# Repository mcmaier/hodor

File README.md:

# HODOR
**H**ighly flexible, **O**pen-source **D**oor **O**peration **R**egulator — HODOR holds your door!

## Overview

HODOR is a universal controller for sliding door and roller shutter motor systems. It drives brushed DC motors (12–24 V) using an ESP32-S3 as the main controller with an H-bridge motor driver. Built-in Wi-Fi makes smart home integration straightforward.

## Repository Structure

This is the main repository containing project-level documentation and release bundles. Hardware and software development happen in dedicated sub-repositories, included here as Git submodules:

| Repository | Description |
|---|---|
| [hodor-hardware](https://github.com/mcmaier/hodor-hardware) | KiCad 9 schematic & PCB design |
| [hodor-software](https://github.com/mcmaier/hodor-software) | ESP-IDF firmware (C, ESP32-S3) |

### Directory Layout

```
hodor/
├── documentation/       Project-level documentation (block diagrams, specs)
├── releases/            Matched HW/SW release bundles
│   └── v0.1.0/          Example: Gerbers + firmware binary for a release
├── hodor-hardware/      Git submodule → mcmaier/hodor-hardware
├── hodor-software/      Git submodule → mcmaier/hodor-software
└── README.md
```

## Getting Started

Clone with submodules:

```bash
git clone --recurse-submodules https://github.com/mcmaier/hodor.git
```

Or, if already cloned:

```bash
git submodule update --init --recursive
```

## Releases

The `releases/` directory contains matched hardware and software versions that are tested together. Each release folder includes the relevant Gerber files, BOM, and firmware binary.

## License

This project is licensed under the MIT License — see the [LICENSE](LICENSE) file for details.

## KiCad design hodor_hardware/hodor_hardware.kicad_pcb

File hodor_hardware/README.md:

# _HODOR - Highly-flexible Open-Source Door Operation Regulator_

Description will be added soon.

## Folder contents

The project **Hodor Hardware** contains hardware design files for the PCBs, which where created in KiCAD 9.0.

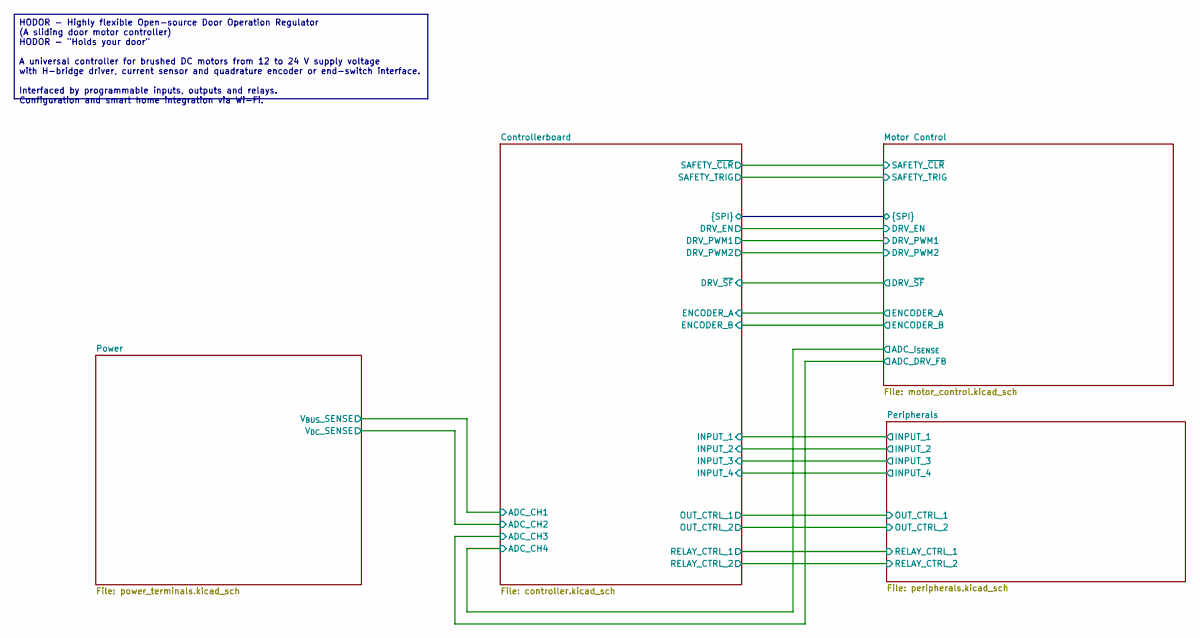
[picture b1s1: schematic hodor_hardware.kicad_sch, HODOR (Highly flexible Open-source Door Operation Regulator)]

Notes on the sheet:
HODOR - Highly flexible Open-source Door Operation Regulator (A sliding door motor controller) HODOR - "Holds your door" A universal controller for brushed DC motors from 12 to 24 V supply voltage with H-bridge driver, current sensor and quadrature encoder or end-switch interface. Interfaced by pro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

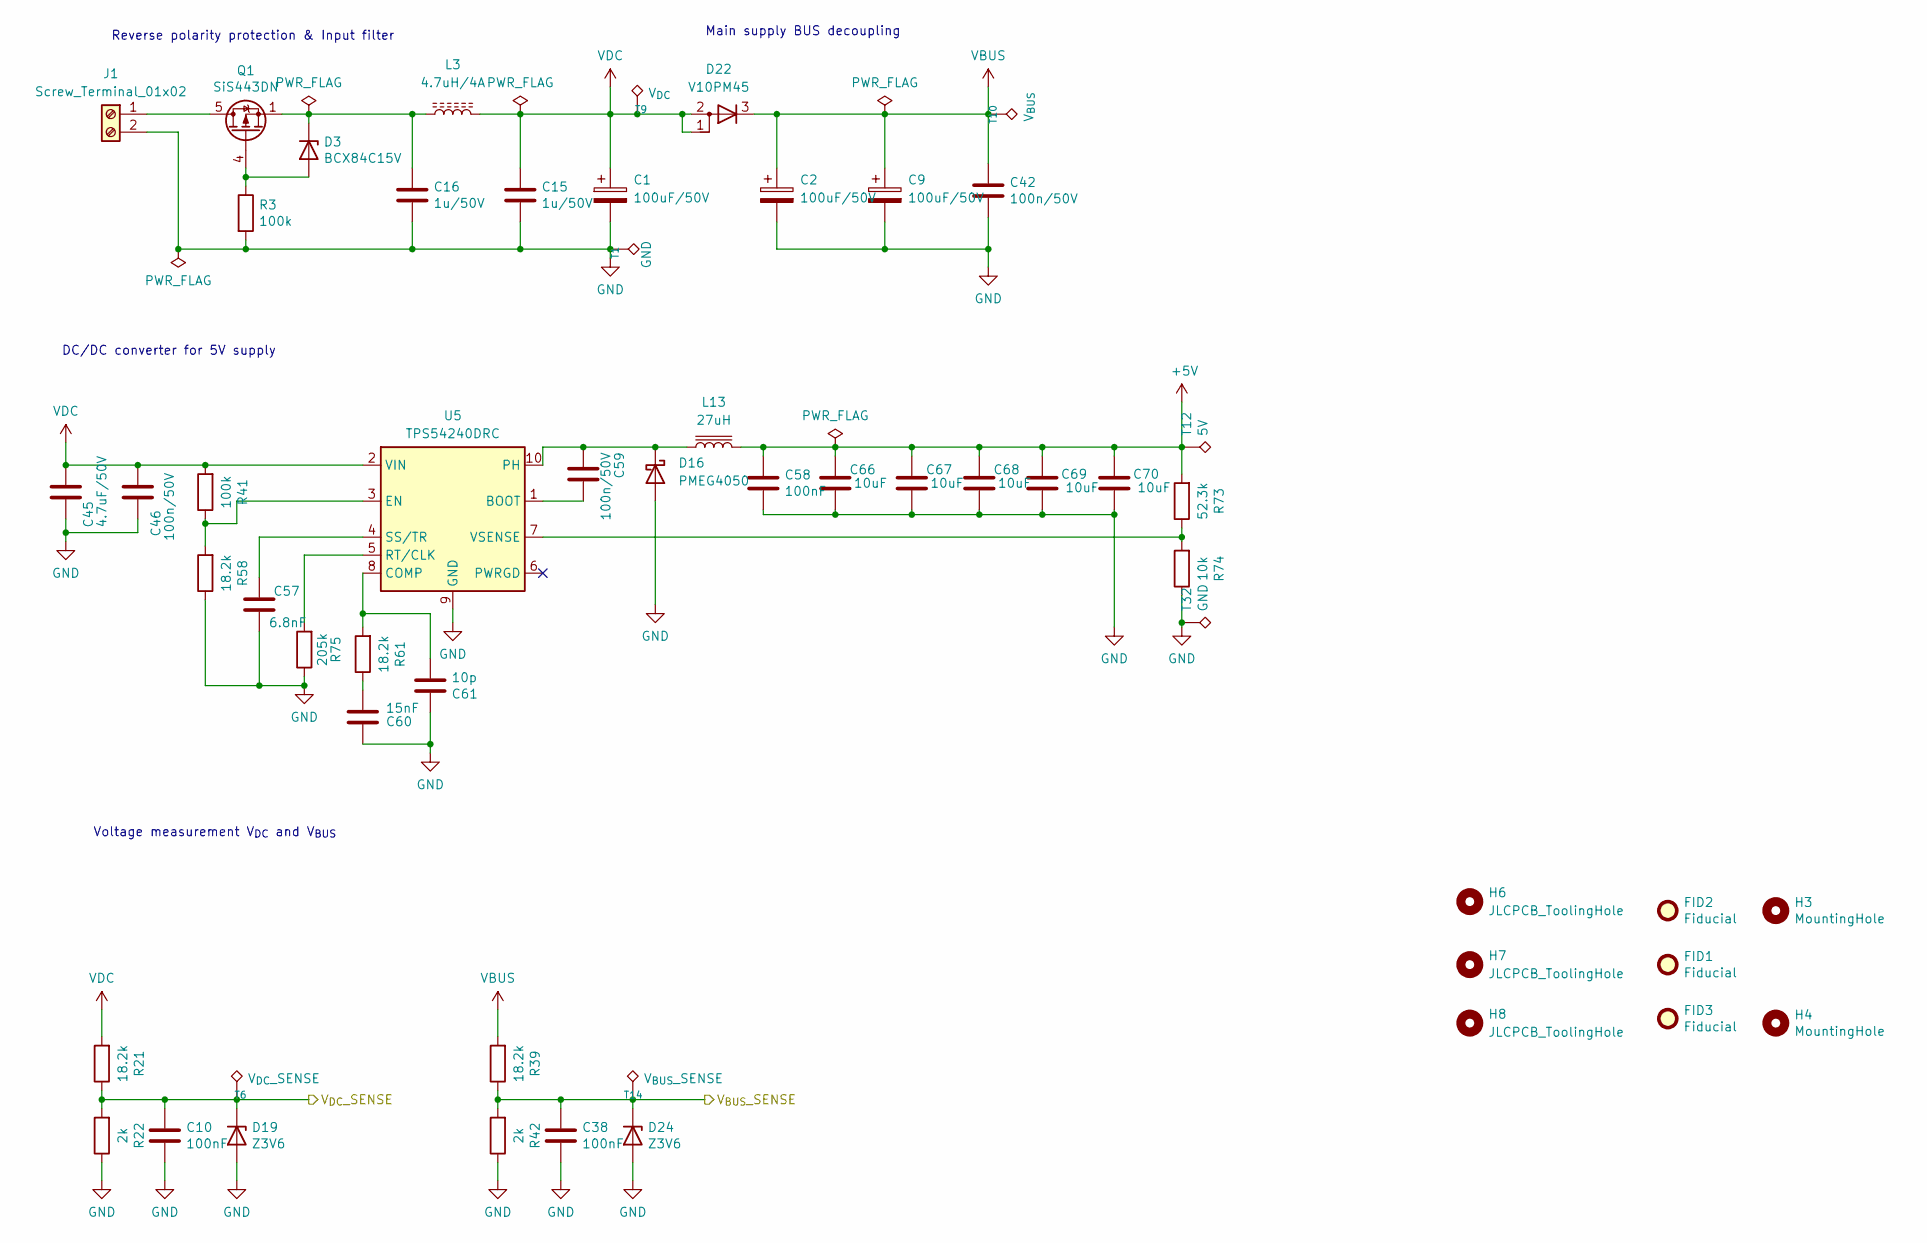
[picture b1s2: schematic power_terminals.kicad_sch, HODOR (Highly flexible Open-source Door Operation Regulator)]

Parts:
C1, C2, C9: 100uF/50V; C_Elec_8x10.2
C10, C38, C58: 100nF; C_0402_1005Metric
C15, C16: 1u/50V; C_0805_2012Metric
C42, C46, C59: 100n/50V; C_0603_1608Metric
C45: 4.7uF/50V; C_1206_3216Metric
C57: 6.8nF; C_0402_1005Metric
C60: 15nF; C_0402_1005Metric
C61: 10p; C_0402_1005Metric
C66, C67, C68, C69, C70: 10uF; C_0805_2012Metric
D3: BCX84C15V; D_SOD-523
D16: PMEG4050; D_SMB
D19, D24: Z3V6; D_SOD-523
D22: V10PM45; TO-277A
FID1, FID2, FID3: Fiducial; Fiducial_1mm_Mask2mm
H3, H4: MountingHole; MountingHole_3.2mm_M3
H6, H7, H8: JLCPCB_ToolingHole
J1: Screw_Terminal_01x02; TerminalBlock_Phoenix_MKDS-1,5-2_1x02_P5.00mm_Horizontal
L3: 4.7uH/4A; L_Wuerth_MAPI-4020
L13: 27uH; L_Wuerth_WE-PD-Typ-7345
Q1: SiS443DN; Vishay_PowerPAK_1212-8_Single
R3, R41: 100k; R_0402_1005Metric
R21, R39, R58, R61: 18.2k; R_0402_1005Metric
R22, R42: 2k; R_0402_1005Metric
R73: 52.3k; R_0402_1005Metric
R74: 10k; R_0402_1005Metric
R75: 205k; R_0402_1005Metric
T1, T32: GND; TestPoint_Pad_1.0x1.0mm
T6: V_{DC}_SENSE; TestPoint_Pad_D1.0mm
T9: V_{DC}; TestPoint_Pad_D1.0mm
T10: V_{BUS}; TestPoint_Pad_D1.0mm
T12: 5V; TestPoint_Pad_D1.0mm
T14: V_{BUS}_SENSE; TestPoint_Pad_D1.0mm
U5: TPS54240DRC; Texas_DRC0010J_ThermalVias

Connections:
+5V: C58.1, C66.1, C67.1, C68.1, C69.1, C70.1, L13.2, R73.2, T12.1; also elsewhere on the board
/Controllerboard/ADC_CH1: C38.1, D24.1 (K), R39.1, R42.2, T14.1; also elsewhere on the board
/Controllerboard/ADC_CH2: C10.1, D19.1 (K), R21.1, R22.2, T6.1; also elsewhere on the board
GND: C1.2, C2.2, C9.2, C10.2, C15.2, C16.2, C38.2, C42.2, C45.2, C46.2, C57.2, C58.2, C60.1, C61.1, C66.2, C67.2, C68.2, C69.2, C70.2, D16.2 (A), D19.2 (A), D24.2 (A), J1.2, R3.2, R22.1, R42.1, R58.1, R74.1, R75.1, T1.1, T32.1, U5.9 (GND), U5.11 (GND); also elsewhere on the board
unnamed: C60.2, R61.1
unnamed: D3.2 (A), Q1.4 (G), R3.1
unnamed: C16.1, D3.1 (K), L3.1, Q1.1 (S), Q1.2 (S), Q1.3 (S)
unnamed: C59.2, D16.1 (K), L13.1, U5.10 (PH)
unnamed: J1.1, Q1.5 (D)
unnamed: C59.1, U5.1 (BOOT)
unnamed: C61.2, R61.2, U5.8 (COMP)
unnamed: R41.1, R58.2, U5.3 (EN)
unnamed: R75.2, U5.5 (RT/CLK)
unnamed: C57.1, U5.4 (SS/TR)
unnamed: R73.1, R74.2, U5.7 (VSENSE)
VBUS: C2.1, C9.1, C42.1, D22.3 (K), R39.2, T10.1; also elsewhere on the board
VDC: C1.1, C15.1, C45.1, C46.1, D22.1 (A), D22.2 (A), L3.2, R21.2, R41.2, T9.1, U5.2 (VIN); also elsewhere on the board

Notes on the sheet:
DC/DC converter for 5V supply
Voltage measurement V_{DC} and V_{BUS}
Reverse polarity protection & Input filter
Main supply BUS decoupling

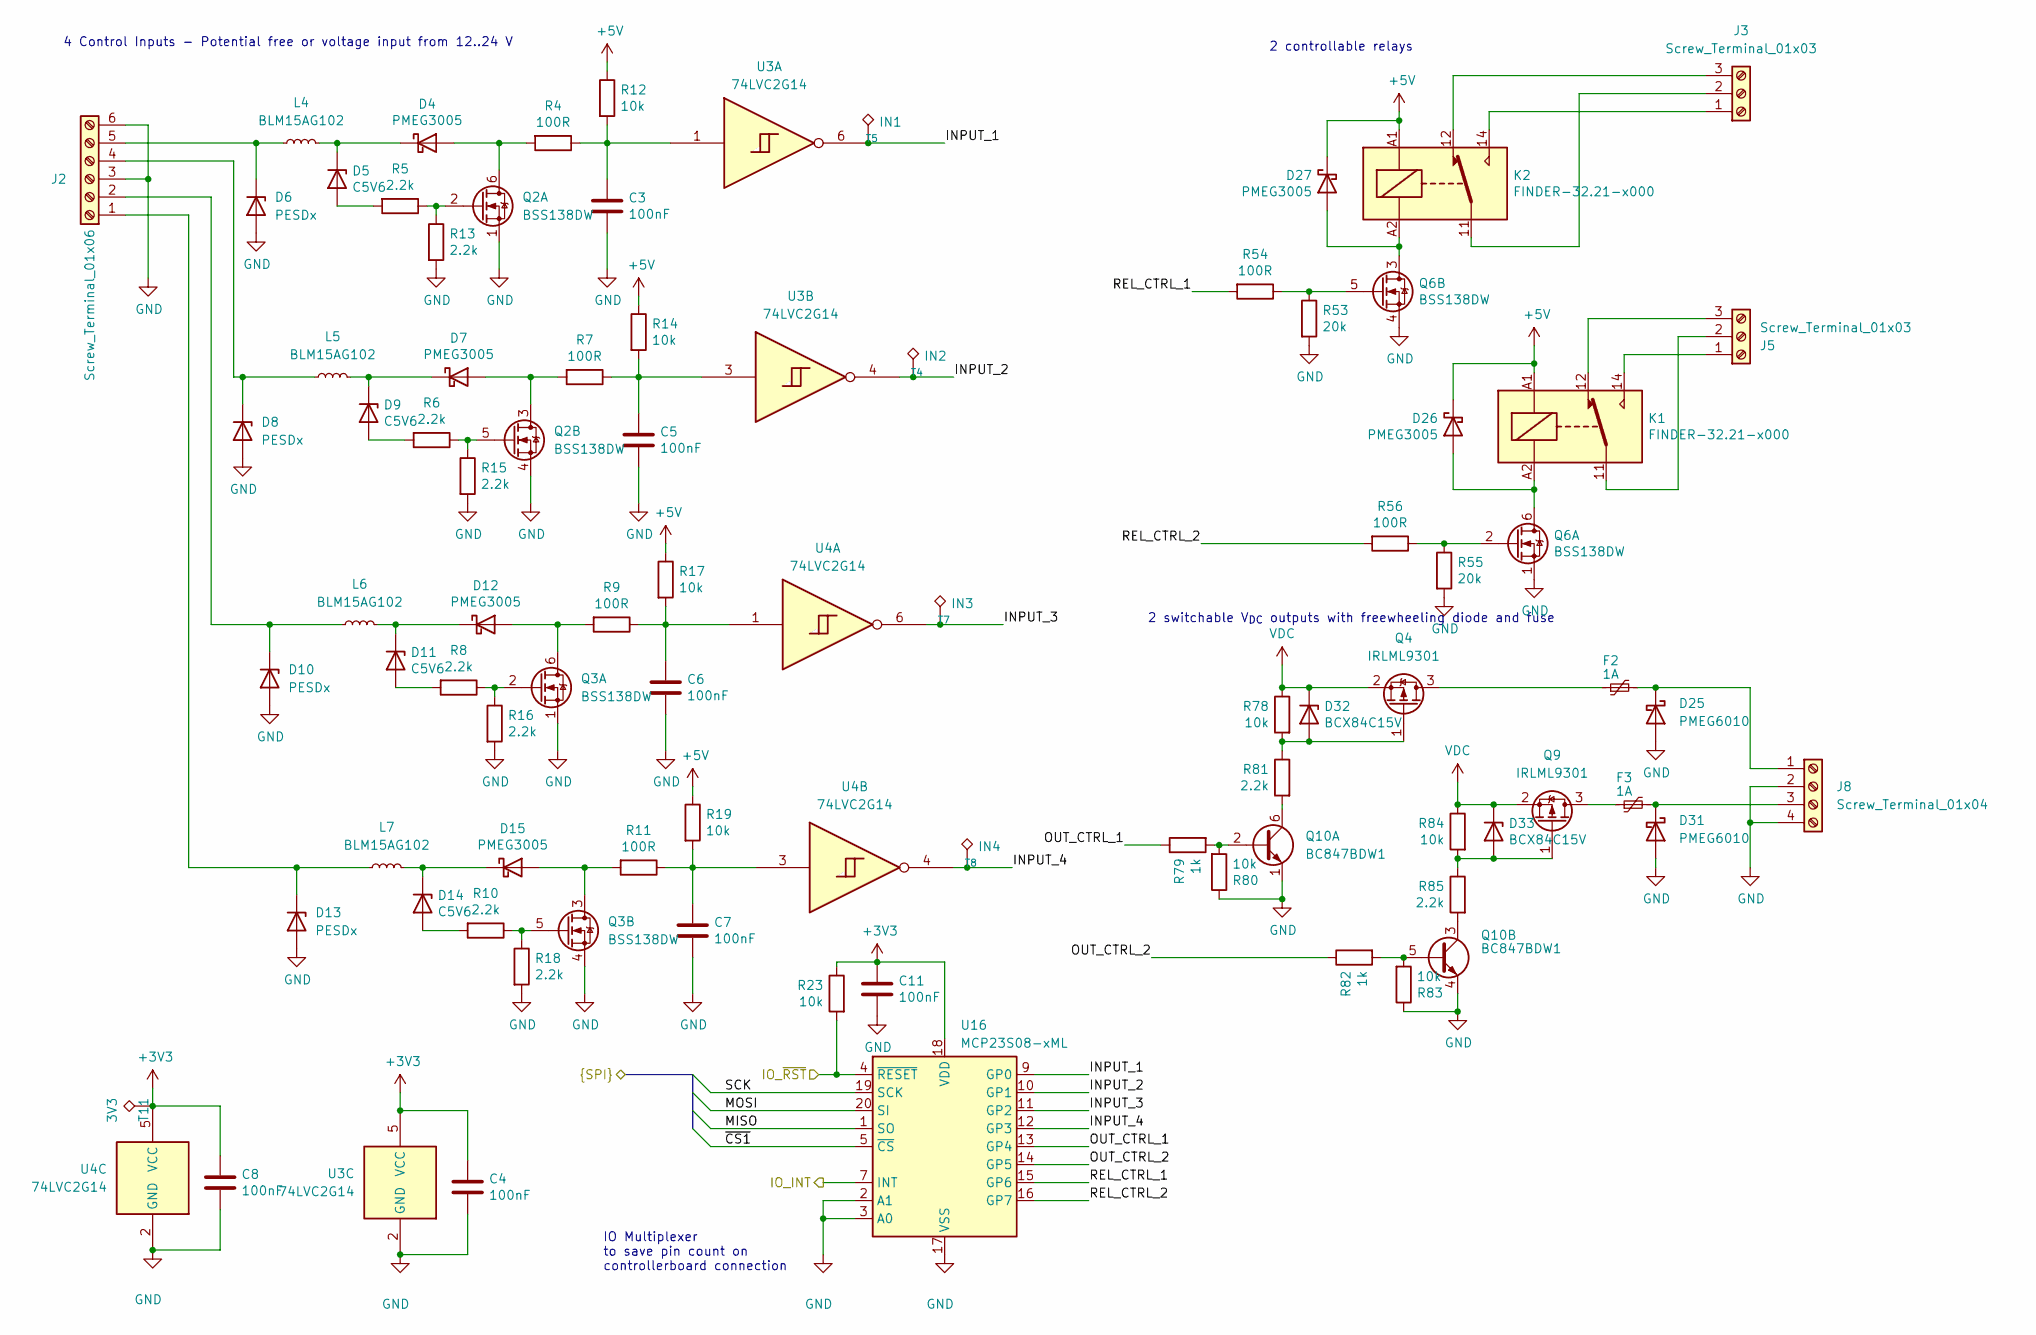
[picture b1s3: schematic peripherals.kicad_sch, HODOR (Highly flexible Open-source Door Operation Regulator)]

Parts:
C3, C4, C5, C6, C7, C8, C11: 100nF; C_0402_1005Metric
D4, D7, D12, D15, D26, D27: PMEG3005; D_SOD-523
D5, D9, D11, D14: C5V6; D_SOD-523
D6, D8, D10, D13: PESDx; Nexperia_DSN1608-2_1.6x0.8mm
D25, D31: PMEG6010; D_SOD-123F
D32, D33: BCX84C15V; D_SOD-523
F2, F3: 1A; Fuse_1210_3225Metric
J2: Screw_Terminal_01x06; TerminalBlock_Phoenix_MKDS-1,5-6_1x06_P5.00mm_Horizontal
J3, J5: Screw_Terminal_01x03; TerminalBlock_Phoenix_MKDS-1,5-3_1x03_P5.00mm_Horizontal
J8: Screw_Terminal_01x04; TerminalBlock_Phoenix_MKDS-1,5-4_1x04_P5.00mm_Horizontal
K1, K2: FINDER-32.21-x000; Relay_SPDT_Finder_32.21-x000
L4, L5, L6, L7: BLM15AG102; L_0402_1005Metric
Q2, Q3, Q6: BSS138DW; SOT-363_SC-70-6
Q4, Q9: IRLML9301; SOT-23
Q10: BC847BDW1; SOT-363_SC-70-6
R4, R7, R9, R11, R54, R56: 100R; R_0402_1005Metric
R5, R6, R8, R10, R13, R15, R16, R18, R81, R85: 2.2k; R_0402_1005Metric
R12, R14, R17, R19, R23, R78, R80, R83, R84: 10k; R_0402_1005Metric
R53, R55: 20k; R_0402_1005Metric
R79, R82: 1k; R_0402_1005Metric
T4: IN2; TestPoint_Pad_D1.0mm
T5: IN1; TestPoint_Pad_D1.0mm
T7: IN3; TestPoint_Pad_D1.0mm
T8: IN4; TestPoint_Pad_D1.0mm
T11: 3V3; TestPoint_Pad_D1.0mm
U3, U4: 74LVC2G14; SOT-23-6
U16: MCP23S08-xML; QFN-20-1EP_4x4mm_P0.5mm_EP2.7x2.7mm

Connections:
+3V3: C4.1, C8.1, C11.1, R23.1, T11.1, U3.5 (VCC), U4.5 (VCC), U16.18 (VDD); also elsewhere on the board
+5V: D26.1 (K), D27.1 (K), K1.A1, K2.A1, R12.1, R14.1, R17.1, R19.1; also elsewhere on the board
/Controllerboard/IO_INT: U16.7 (INT); also elsewhere on the board
/Controllerboard/IO_~RST: R23.2, U16.4 (~RESET); also elsewhere on the board
/Controllerboard/MISO: U16.1 (SO); also elsewhere on the board
/Controllerboard/MOSI: U16.20 (SI); also elsewhere on the board
/Controllerboard/SCK: U16.19 (SCK); also elsewhere on the board
/Controllerboard/~CS1: U16.5 (~CS); also elsewhere on the board
/Peripherals/INPUT_1: T5.1, U3.6, U16.9 (GP0)
/Peripherals/INPUT_2: T4.1, U3.4, U16.10 (GP1)
/Peripherals/INPUT_3: T7.1, U4.6, U16.11 (GP2)
/Peripherals/INPUT_4: T8.1, U4.4, U16.12 (GP3)
/Peripherals/OUT_CTRL_1: R79.1, U16.13 (GP4)
/Peripherals/OUT_CTRL_2: R82.1, U16.14 (GP5)
/Peripherals/REL_CTRL_1: R54.2, U16.15 (GP6)
/Peripherals/REL_CTRL_2: R56.2, U16.16 (GP7)
GND: C3.2, C4.2, C5.2, C6.2, C7.2, C8.2, C11.2, D6.2 (A), D8.2 (A), D10.2 (A), D13.2 (A), D25.2 (A), D31.2 (A), J2.3, J2.6, J8.2, J8.4, Q2.1 (S), Q2.4 (S), Q3.1 (S), Q3.4 (S), Q6.1 (S), Q6.4 (S), Q10.1 (E1), Q10.4 (E2), R13.2, R15.2, R16.2, R18.2, R53.2, R55.2, R80.1, R83.1, U3.2 (GND), U4.2 (GND), U16.2 (A1), U16.3 (A0), U16.17 (VSS); also elsewhere on the board
unnamed: C3.1, R4.1, R12.2, U3.1
unnamed: C5.1, R7.1, R14.2, U3.3
unnamed: C6.1, R9.1, R17.2, U4.1
unnamed: C7.1, R11.1, R19.2, U4.3
unnamed: D4.2 (A), Q2.6 (D), R4.2
unnamed: D4.1 (K), D5.1 (K), L4.2
unnamed: D5.2 (A), R5.2
unnamed: D6.1 (K), J2.5, L4.1
unnamed: D7.2 (A), Q2.3 (D), R7.2
unnamed: D7.1 (K), D9.1 (K), L5.2
unnamed: D8.1 (K), J2.4, L5.1
unnamed: D9.2 (A), R6.2
unnamed: D10.1 (K), J2.2, L6.1
unnamed: D11.2 (A), R8.2
unnamed: D11.1 (K), D12.1 (K), L6.2
unnamed: D12.2 (A), Q3.6 (D), R9.2
unnamed: D13.1 (K), J2.1, L7.1
unnamed: D14.2 (A), R10.2
unnamed: D14.1 (K), D15.1 (K), L7.2
unnamed: D15.2 (A), Q3.3 (D), R11.2
unnamed: D25.1 (K), F2.2, J8.1
unnamed: D26.2 (A), K1.A2, Q6.6 (D)
unnamed: D27.2 (A), K2.A2, Q6.3 (D)
unnamed: D31.1 (K), F3.2, J8.3
unnamed: D32.2 (A), Q4.1 (G), R78.2, R81.1
unnamed: D33.2 (A), Q9.1 (G), R84.2, R85.1
unnamed: J3.1, K2.14
unnamed: J3.2, K2.11
unnamed: J3.3, K2.12
unnamed: J5.1, K1.14
unnamed: J5.2, K1.11
unnamed: J5.3, K1.12
unnamed: Q2.2 (G), R5.1, R13.1
unnamed: Q2.5 (G), R6.1, R15.1
unnamed: Q3.2 (G), R8.1, R16.1
unnamed: Q3.5 (G), R10.1, R18.1
unnamed: F2.1, Q4.3 (D)
unnamed: Q6.2 (G), R55.1, R56.1
unnamed: Q6.5 (G), R53.1, R54.1
unnamed: F3.1, Q9.3 (D)
unnamed: Q10.2 (B1), R79.2, R80.2
unnamed: Q10.6 (C1), R81.2
unnamed: Q10.5 (B2), R82.2, R83.2
unnamed: Q10.3 (C2), R85.2
VDC: D32.1 (K), D33.1 (K), Q4.2 (S), Q9.2 (S), R78.1, R84.1; also elsewhere on the board

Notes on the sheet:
4 Control Inputs - Potential free or voltage input from 12..24 V
2 controllable relays
2 switchable V_{DC} outputs with freewheeling diode and fuse
IO Multiplexer to save pin count on controllerboard connection

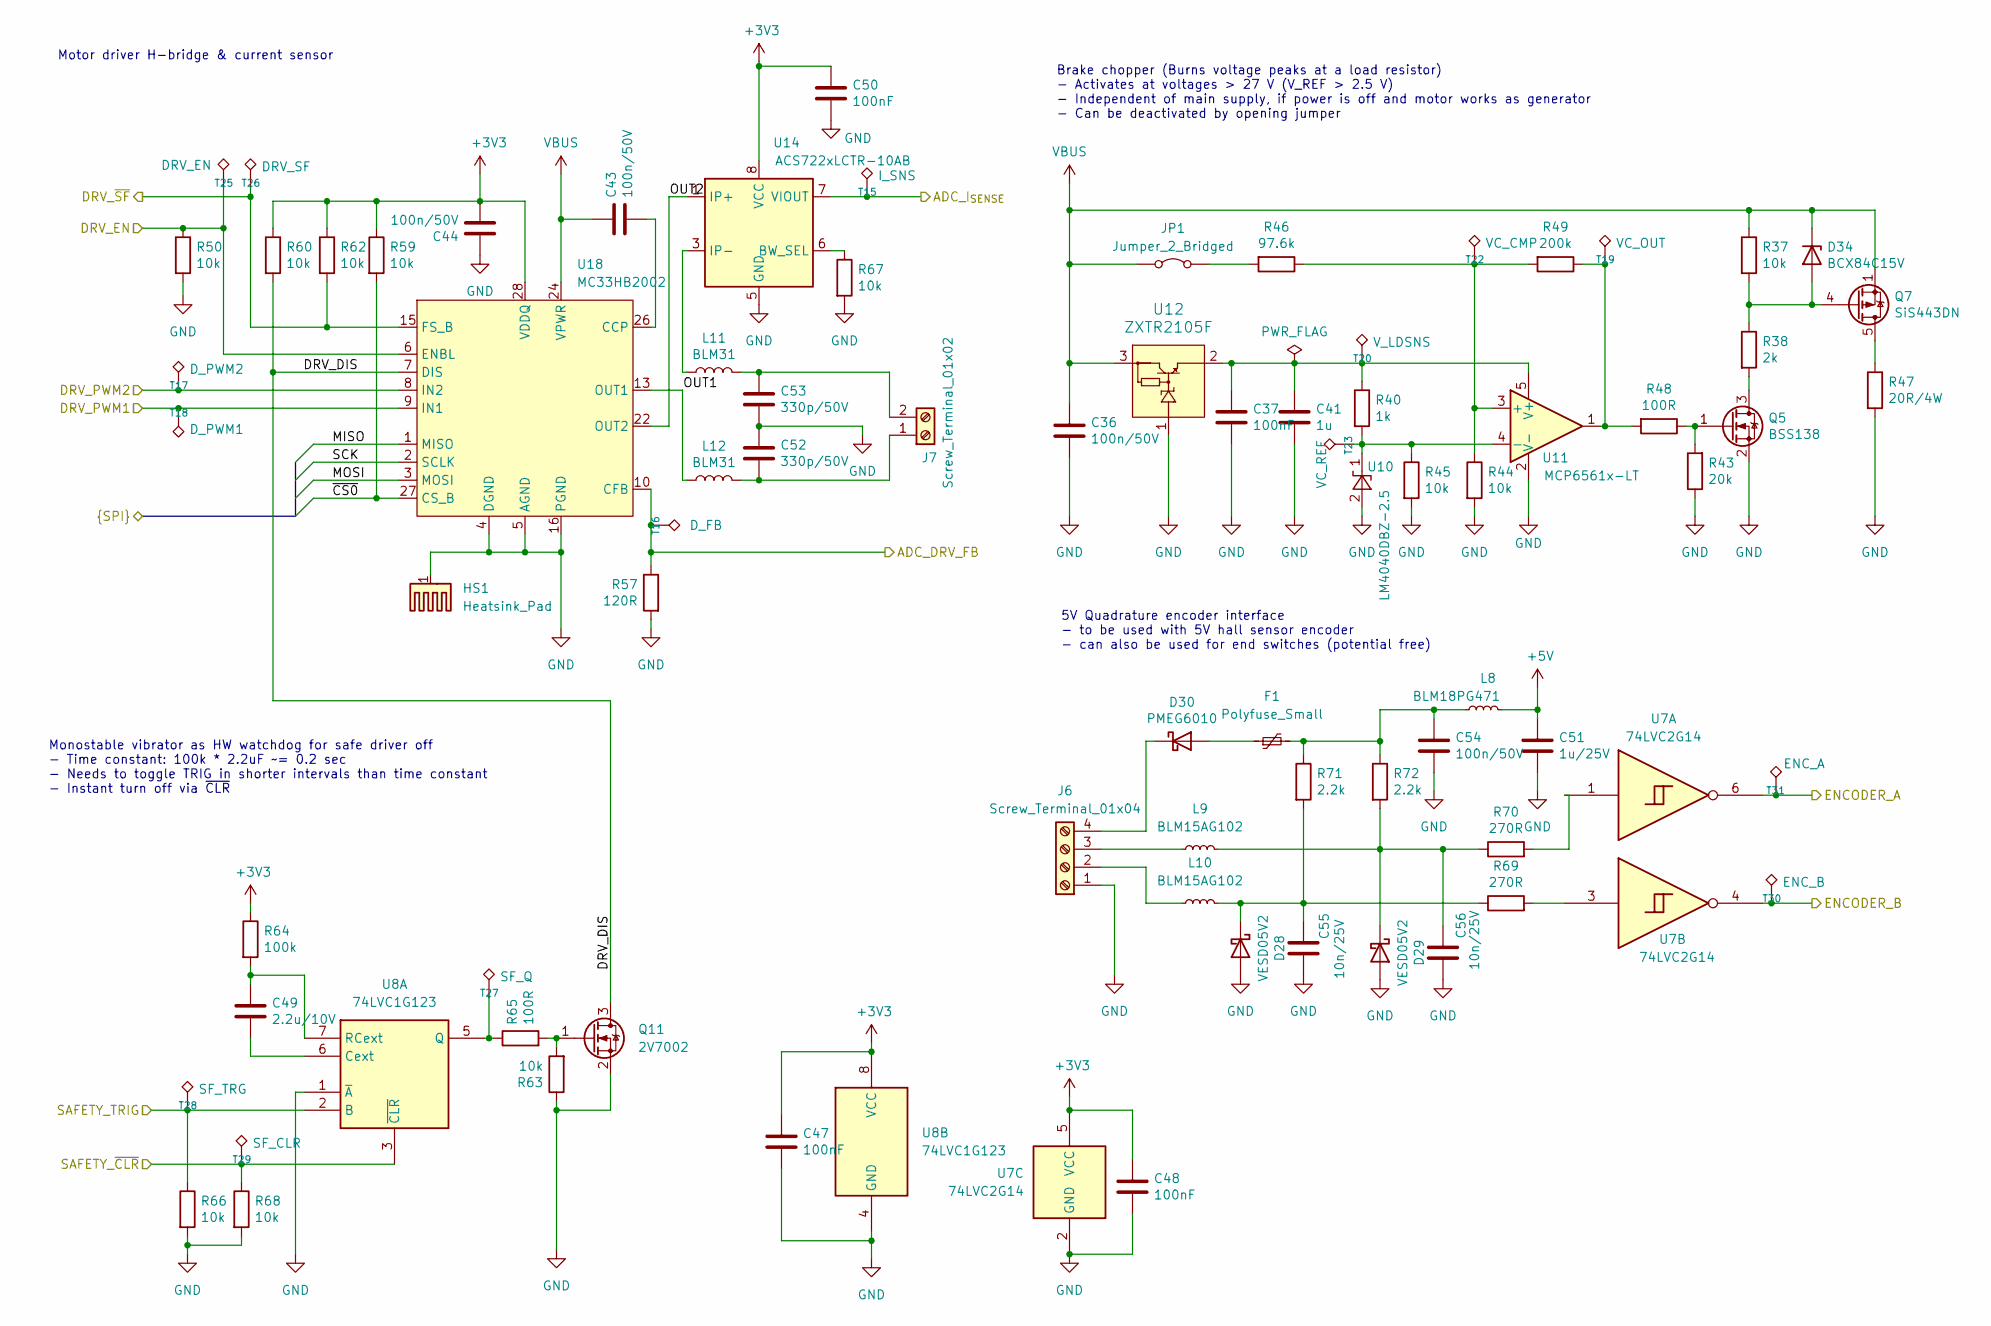
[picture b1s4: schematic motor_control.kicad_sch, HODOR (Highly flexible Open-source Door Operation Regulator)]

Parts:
C36, C43, C44, C54: 100n/50V; C_0603_1608Metric
C37, C47, C48, C50: 100nF; C_0402_1005Metric
C41: 1u; C_0402_1005Metric
C49: 2.2u/10V; C_0603_1608Metric
C51: 1u/25V; C_0603_1608Metric
C52, C53: 330p/50V; C_0603_1608Metric
C55, C56: 10n/25V; C_0402_1005Metric
D28, D29: VESD05V2; D_SOD-523
D30: PMEG6010; D_SOD-123F
D34: BCX84C15V; D_SOD-523
F1: Polyfuse_Small; Fuse_0805_2012Metric
HS1: Heatsink_Pad; Heatsink_AAVID_573300D00010G_TO-263
J6: Screw_Terminal_01x04; TerminalBlock_Phoenix_MKDS-1,5-4_1x04_P5.00mm_Horizontal
J7: Screw_Terminal_01x02; TerminalBlock_Phoenix_MKDS-1,5-2_1x02_P5.00mm_Horizontal
JP1: Jumper_2_Bridged; SolderJumper-2_P1.3mm_Bridged_Pad1.0x1.5mm
L8: BLM18PG471; L_0603_1608Metric
L9, L10: BLM15AG102; L_0402_1005Metric
L11, L12: BLM31; L_1206_3216Metric
Q5: BSS138; SOT-23
Q7: SiS443DN; Vishay_PowerPAK_1212-8_Single
Q11: 2V7002; SOT-323_SC-70
R37, R44, R45, R50, R59, R60, R62, R63, R66, R67, R68: 10k; R_0402_1005Metric
R38: 2k; R_0805_2012Metric
R40: 1k; R_0402_1005Metric
R43: 20k; R_0402_1005Metric
R46: 97.6k; R_0402_1005Metric
R47: 20R/4W; R_2816_7142Metric
R48, R65: 100R; R_0402_1005Metric
R49: 200k; R_0402_1005Metric
R57: 120R; R_0603_1608Metric
R64: 100k; R_0402_1005Metric
R69, R70: 270R; R_0402_1005Metric
R71, R72: 2.2k; R_0402_1005Metric
T15: I_SNS; TestPoint_Pad_D1.0mm
T16: D_FB; TestPoint_Pad_D1.0mm
T17: D_PWM2; TestPoint_Pad_D1.0mm
T18: D_PWM1; TestPoint_Pad_D1.0mm
T19: VC_OUT; TestPoint_Pad_D1.0mm
T20: V_LDSNS; TestPoint_Pad_D1.0mm
T22: VC_CMP; TestPoint_Pad_D1.0mm
T23: VC_REF; TestPoint_Pad_D1.0mm
T25: DRV_EN; TestPoint_Pad_D1.0mm
T26: DRV_SF; TestPoint_Pad_D1.0mm
T27: SF_Q; TestPoint_Pad_D1.0mm
T28: SF_TRG; TestPoint_Pad_D1.0mm
T29: SF_CLR; TestPoint_Pad_D1.0mm
T30: ENC_B; TestPoint_Pad_D1.0mm
T31: ENC_A; TestPoint_Pad_D1.0mm
U7: 74LVC2G14; SOT-23-6
U8: 74LVC1G123; VSSOP-8_2.3x2mm_P0.5mm
U10: LM4040DBZ-2.5; SOT-23
U11: MCP6561x-LT; SOT-353_SC-70-5
U12: ZXTR2105F; SOT-23
U14: ACS722xLCTR-10AB; SOIC-8_3.9x4.9mm_P1.27mm
U18: MC33HB2002; HVQFN-28-1EP_6x6mm_MC33HB2002

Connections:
+3V3: C44.2, C47.1, C48.1, C50.1, R59.1, R60.1, R62.1, R64.1, U7.5 (VCC), U8.8 (VCC), U14.8 (VCC), U18.28 (VDDQ); also elsewhere on the board
+5V: C51.1, L8.2; also elsewhere on the board
/Controllerboard/ADC_CH3: R57.1, T16.1, U18.10 (CFB); also elsewhere on the board
/Controllerboard/ADC_CH4: T15.1, U14.7 (VIOUT); also elsewhere on the board
/Controllerboard/DRV_EN: R50.1, T25.1, U18.6 (ENBL); also elsewhere on the board
/Controllerboard/DRV_PWM1: T18.1, U18.9 (IN1); also elsewhere on the board
/Controllerboard/DRV_PWM2: T17.1, U18.8 (IN2); also elsewhere on the board
/Controllerboard/DRV_~SF: R62.2, T26.1, U18.15 (FS_B); also elsewhere on the board
/Controllerboard/ENCODER_A: T31.1, U7.6; also elsewhere on the board
/Controllerboard/ENCODER_B: T30.1, U7.4; also elsewhere on the board
/Controllerboard/MISO: U18.1 (MISO); also elsewhere on the board
/Controllerboard/MOSI: U18.3 (MOSI); also elsewhere on the board
/Controllerboard/SAFETY_TRIG: R66.1, T28.1, U8.2 (B); also elsewhere on the board
/Controllerboard/SAFETY_~CLR: R68.1, T29.1, U8.3 (~CLR); also elsewhere on the board
/Controllerboard/SCK: U18.2 (SCLK); also elsewhere on the board
/Controllerboard/~CS0: R59.2, U18.27 (CS_B); also elsewhere on the board
/Motor Control/DRV_DIS: Q11.3 (D), R60.2, U18.7 (DIS)
/Motor Control/OUT1: L12.1, U18.13 (OUT1), U18.14 (OUT1)
/Motor Control/OUT2: U14.1 (IP+), U14.2 (IP+), U18.22 (OUT2), U18.23 (OUT2)
GND: C36.2, C37.2, C41.2, C44.1, C47.2, C48.2, C50.2, C51.2, C52.1, C53.2, C54.2, C55.2, C56.2, D28.2 (A), D29.2 (A), HS1.1, J6.1, Q5.2 (S), Q11.2 (S), R43.1, R44.2, R45.2, R47.2, R50.2, R57.2, R63.1, R66.2, R67.2, R68.2, U7.2 (GND), U8.1 (~A), U8.4 (GND), U10.2 (A), U11.2 (V-), U12.1 (GND), U14.5 (GND), U18.4 (DGND), U18.5 (AGND), U18.16 (PGND), U18.17 (PGND), U18.18 (PGND), U18.19 (PGND), U18.20 (PGND), U18.21 (AGND), U18.29 (AGND); also elsewhere on the board
unnamed: C54.1, F1.2, L8.1, R71.1, R72.1
unnamed: C55.1, D28.1 (K), L10.2, R69.1, R71.2
unnamed: C56.1, D29.1 (K), L9.2, R70.1, R72.2
unnamed: D30.2 (A), F1.1
unnamed: D30.1 (K), J6.4
unnamed: D34.2 (A), Q7.4 (G), R37.2, R38.1
unnamed: J6.2, L10.1
unnamed: J6.3, L9.1
unnamed: C52.2, J7.1, L12.2
unnamed: C53.1, J7.2, L11.2
unnamed: JP1.2 (B), R46.2
unnamed: L11.1, U14.3 (IP-), U14.4 (IP-)
unnamed: Q5.3 (D), R38.2
unnamed: Q5.1 (G), R43.2, R48.1
unnamed: Q7.5 (D), R47.1
unnamed: Q11.1 (G), R63.2, R65.2
unnamed: R48.2, R49.1, T19.1, U11.1
unnamed: R69.2, U7.3
unnamed: R70.2, U7.1
unnamed: C49.2, U8.6 (Cext)
unnamed: R65.1, T27.1, U8.5 (Q)
unnamed: C49.1, R64.2, U8.7 (RCext)
unnamed: R40.2, R45.1, T23.1, U10.1 (K), U11.4 (-)
unnamed: R44.1, R46.1, R49.2, T22.1, U11.3 (+)
unnamed: C37.1, C41.1, R40.1, T20.1, U11.5 (V+), U12.2 (VOUT)
unnamed: R67.1, U14.6 (BW_SEL)
unnamed: C43.2, U18.26 (CCP)
VBUS: C36.1, C43.1, D34.1 (K), JP1.1 (A), Q7.1 (S), Q7.2 (S), Q7.3 (S), R37.1, U12.3 (VIN), U18.11 (VPWR), U18.12 (VPWR), U18.24 (VPWR), U18.25 (VPWR); also elsewhere on the board

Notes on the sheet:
Brake chopper (Burns voltage peaks at a load resistor) - Activates at voltages > 27 V (V_REF > 2.5 V) - Independent of main supply, if power is off and motor works as generator - Can be deactivated by opening jumper
5V Quadrature encoder interface - to be used with 5V hall sensor encoder - can also be used for end switches (potential free)
Motor driver H-bridge & current sensor
Monostable vibrator as HW watchdog for safe driver off - Time constant: 100k * 2.2uF ~= 0.2 sec - Needs to toggle TRIG in shorter intervals than time constant - Instant turn off via ~{CLR}

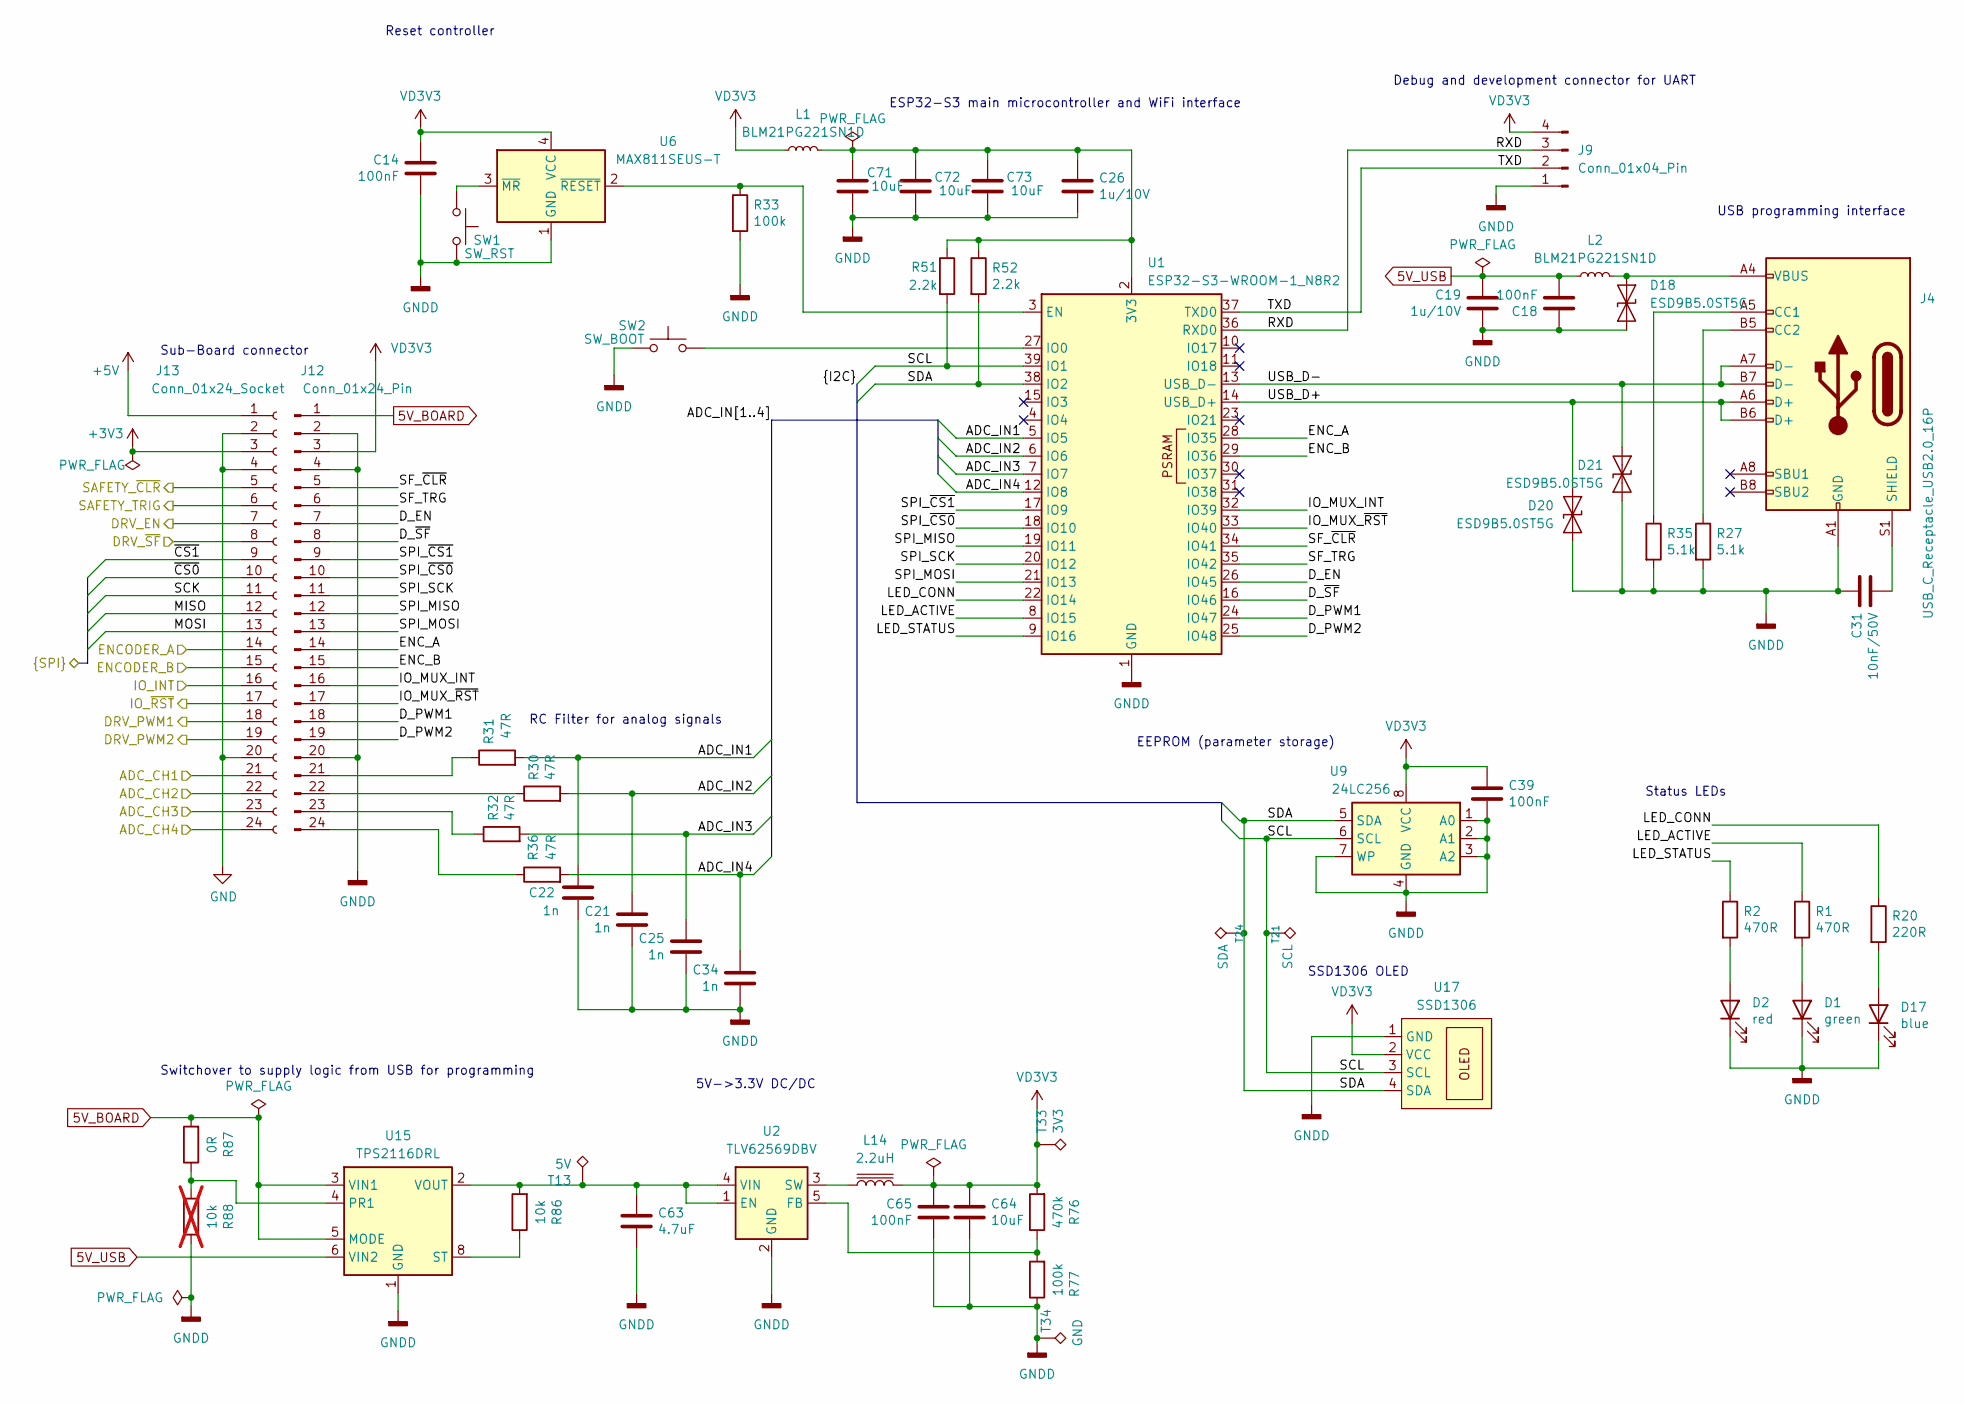
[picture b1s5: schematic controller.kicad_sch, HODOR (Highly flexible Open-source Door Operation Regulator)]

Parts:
C14, C18, C39, C65: 100nF; C_0402_1005Metric
C19, C26: 1u/10V; C_0402_1005Metric
C21, C22, C25, C34: 1n; C_0402_1005Metric
C31: 10nF/50V; C_0402_1005Metric
C63: 4.7uF; C_1206_3216Metric
C64, C71, C72, C73: 10uF; C_0805_2012Metric
D1: green; LED_Kingbright_APA1606_1.6x0.6mm_Horizontal
D2: red; LED_Kingbright_APA1606_1.6x0.6mm_Horizontal
D17: blue; LED_Kingbright_APA1606_1.6x0.6mm_Horizontal
D18, D20, D21: ESD9B5.0ST5G; D_SOD-923
J4: USB_C_Receptacle_USB2.0_16P; USB_C_Receptacle_G-Switch_GT-USB-7010ASV
J9: Conn_01x04_Pin; Conn_Header2.54_1x04_SMD
J12: Conn_01x24_Pin; PinHeader_2x12_P2.00mm_Horizontal
J13: Conn_01x24_Socket; PinSocket_2x12_P2.00mm_Vertical
L1, L2: BLM21PG221SN1D; L_0805_2012Metric
L14: 2.2uH; L_1812_4532Metric
R1, R2: 470R; R_0402_1005Metric
R20: 220R; R_0402_1005Metric
R27, R35: 5.1k; R_0402_1005Metric
R30, R31, R32, R36: 47R; R_0402_1005Metric
R33, R77: 100k; R_0402_1005Metric
R51, R52: 2.2k; R_0402_1005Metric
R76: 470k; R_0402_1005Metric
R86: 10k; R_0402_1005Metric
R87: 0R; R_0402_1005Metric
R88: 10k; R_0402_1005Metric; not fitted
SW1: SW_RST; SW_SPST_CK_KMS2xxG
SW2: SW_BOOT; SW_SPST_CK_KMS2xxG
T13: 5V; TestPoint_Pad_D1.0mm
T21: SCL; TestPoint_Pad_D1.0mm
T24: SDA; TestPoint_Pad_D1.0mm
T33: 3V3; TestPoint_Pad_D1.0mm
T34: GND; TestPoint_Pad_1.0x1.0mm
U1: ESP32-S3-WROOM-1_N8R2; ESP32-S3-WROOM-1
U2: TLV62569DBV; SOT-23-5
U6: MAX811SEUS-T; SOT-143
U9: 24LC256; TSSOP-8_4.4x3mm_P0.65mm
U15: TPS2116DRL; SOT-583-8
U17: SSD1306; SSD1306_OLED_Horizontal_Reverse

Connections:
5V_BOARD: J12.1, R87.2, U15.3 (VIN1), U15.5 (MODE)
5V_USB: C18.1, C19.2, L2.1, U15.6 (VIN2)
+3V3: J13.3; also elsewhere on the board
+5V: J13.1; also elsewhere on the board
/Controllerboard/ADC_CH1: J13.21; also elsewhere on the board
/Controllerboard/ADC_CH2: J13.22; also elsewhere on the board
/Controllerboard/ADC_CH3: J13.23; also elsewhere on the board
/Controllerboard/ADC_CH4: J13.24; also elsewhere on the board
/Controllerboard/ADC_IN1: C22.2, R31.2, U1.5 (IO5)
/Controllerboard/ADC_IN2: C21.2, R30.2, U1.6 (IO6)
/Controllerboard/ADC_IN3: C25.2, R32.2, U1.7 (IO7)
/Controllerboard/ADC_IN4: C34.2, R36.2, U1.12 (IO8)
/Controllerboard/DRV_EN: J13.7; also elsewhere on the board
/Controllerboard/DRV_PWM1: J13.18; also elsewhere on the board
/Controllerboard/DRV_PWM2: J13.19; also elsewhere on the board
/Controllerboard/DRV_~SF: J13.8; also elsewhere on the board
/Controllerboard/D_EN: J12.7, U1.26 (IO45)
/Controllerboard/D_PWM1: J12.18, U1.24 (IO47)
/Controllerboard/D_PWM2: J12.19, U1.25 (IO48)
/Controllerboard/D_~SF: J12.8, U1.16 (IO46)
/Controllerboard/ENCODER_A: J13.14; also elsewhere on the board
/Controllerboard/ENCODER_B: J13.15; also elsewhere on the board
/Controllerboard/ENC_A: J12.14, U1.28 (IO35)
/Controllerboard/ENC_B: J12.15, U1.29 (IO36)
/Controllerboard/IO_INT: J13.16; also elsewhere on the board
/Controllerboard/IO_MUX_INT: J12.16, U1.32 (IO39)
/Controllerboard/IO_MUX_~RST: J12.17, U1.33 (IO40)
/Controllerboard/IO_~RST: J13.17; also elsewhere on the board
/Controllerboard/LED_ACTIVE: R1.1, U1.8 (IO15)
/Controllerboard/LED_CONN: R20.1, U1.22 (IO14)
/Controllerboard/LED_STATUS: R2.1, U1.9 (IO16)
/Controllerboard/MISO: J13.12; also elsewhere on the board
/Controllerboard/MOSI: J13.13; also elsewhere on the board
/Controllerboard/RXD: J9.3, U1.36 (RXD0)
/Controllerboard/SAFETY_TRIG: J13.6; also elsewhere on the board
/Controllerboard/SAFETY_~CLR: J13.5; also elsewhere on the board
/Controllerboard/SCK: J13.11; also elsewhere on the board
/Controllerboard/SCL: R51.2, T21.1, U1.39 (IO1), U9.6 (SCL), U17.3 (SCL)
/Controllerboard/SDA: R52.2, T24.1, U1.38 (IO2), U9.5 (SDA), U17.4 (SDA)
/Controllerboard/SF_TRG: J12.6, U1.35 (IO42)
/Controllerboard/SF_~CLR: J12.5, U1.34 (IO41)
/Controllerboard/SPI_MISO: J12.12, U1.19 (IO11)
/Controllerboard/SPI_MOSI: J12.13, U1.21 (IO13)
/Controllerboard/SPI_SCK: J12.11, U1.20 (IO12)
/Controllerboard/SPI_~CS0: J12.10, U1.18 (IO10)
/Controllerboard/SPI_~CS1: J12.9, U1.17 (IO9)
/Controllerboard/TXD: J9.2, U1.37 (TXD0)
/Controllerboard/USB_D+: D20.2 (A2), J4.A6 (D+), J4.B6 (D+), U1.14 (USB_D+)
/Controllerboard/USB_D-: D21.2 (A2), J4.A7 (D-), J4.B7 (D-), U1.13 (USB_D-)
/Controllerboard/~CS0: J13.10; also elsewhere on the board
/Controllerboard/~CS1: J13.9; also elsewhere on the board
GND: J13.2, J13.4, J13.20; also elsewhere on the board
GNDD: C14.1, C18.2, C19.1, C21.1, C22.1, C25.1, C26.1, C31.2, C34.1, C39.1, C63.2, C64.2, C65.2, C71.2, C72.2, C73.2, D1.1 (K), D2.1 (K), D17.1 (K), D18.1 (A1), D20.1 (A1), D21.1 (A1), J4.A1 (GND), J4.A12 (GND), J4.B1 (GND), J4.B12 (GND), J9.1, J12.2, J12.4, J12.20, R27.2, R33.2, R35.2, R77.1, R88.1, SW1.1, SW2.1, T34.1, U1.1 (GND), U1.40 (GND), U1.41 (GND), U2.2 (GND), U6.1 (GND), U9.1 (A0), U9.2 (A1), U9.3 (A2), U9.4 (GND), U9.7 (WP), U15.1 (GND), U17.1 (GND)
unnamed: D1.2 (A), R1.2
unnamed: D2.2 (A), R2.2
unnamed: D17.2 (A), R20.2
unnamed: D18.2 (A2), J4.A4 (VBUS), J4.A9 (VBUS), J4.B4 (VBUS), J4.B9 (VBUS), L2.2
unnamed: J4.A5 (CC1), R35.1
unnamed: J4.B5 (CC2), R27.1
unnamed: C31.1, J4.S1 (SHIELD)
unnamed: J12.21, R31.1
unnamed: J12.22, R30.1
unnamed: J12.23, R32.1
unnamed: J12.24, R36.1
unnamed: C26.2, C71.1, C72.1, C73.1, L1.2, R51.1, R52.1, U1.2 (3V3)
unnamed: R33.1, U1.3 (EN), U6.2 (~RESET)
unnamed: SW2.2, U1.27 (IO0)
unnamed: C63.1, R86.2, T13.1, U2.1 (EN), U2.4 (VIN), U15.2 (VOUT), U15.7 (VOUT)
unnamed: R76.1, R77.2, U2.5 (FB)
unnamed: L14.1, U2.3 (SW)
unnamed: SW1.2, U6.3 (~MR)
unnamed: R87.1, R88.2, U15.4 (PR1)
unnamed: R86.1, U15.8 (ST)
VD3V3: C14.2, C39.2, C64.1, C65.1, J9.4, J12.3, L1.1, L14.2, R76.2, T33.1, U6.4 (VCC), U9.8 (VCC), U17.2 (VCC)

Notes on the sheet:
Status LEDs
RC Filter for analog signals
SSD1306 OLED
Debug and development connector for UART
Switchover to supply logic from USB for programming
EEPROM (parameter storage)
Sub-Board connector
ESP32-S3 main microcontroller and WiFi interface
USB programming interface
Reset controller
5V->3.3V DC/DC

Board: 2 copper layers, 274 parts (2 on the bottom side), 169 nets, no tracks yet.
